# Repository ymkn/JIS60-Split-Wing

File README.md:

# JIS60-Split Wing

60% sized JIS layout split keyboard.

## Default Layout

Powered by RP2040 with [KMK Firmware](http://kmkfw.io/). Fully customizable.

## Build Guide

See [doc/build-guide.md](doc/build-guide.md)

## License

This project is licensed under the MIT License, see the [LICENSE file](LICENSE) for details.

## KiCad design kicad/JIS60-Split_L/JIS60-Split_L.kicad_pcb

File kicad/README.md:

# KiCAD source files

## KiCAD version

7.x or higher is required.

## dependencies

- https://github.com/crides/kleeb
  - rp2040-zero
- https://github.com/yskoht/kicad-MJ-4PP-9
  - TRRS Connector
- https://github.com/kiswitch/kiswitch
  - Keyswitch and Stab
- https://github.com/Salicylic-acid3/KiCAD_FootPrint
  - Mounting Hole

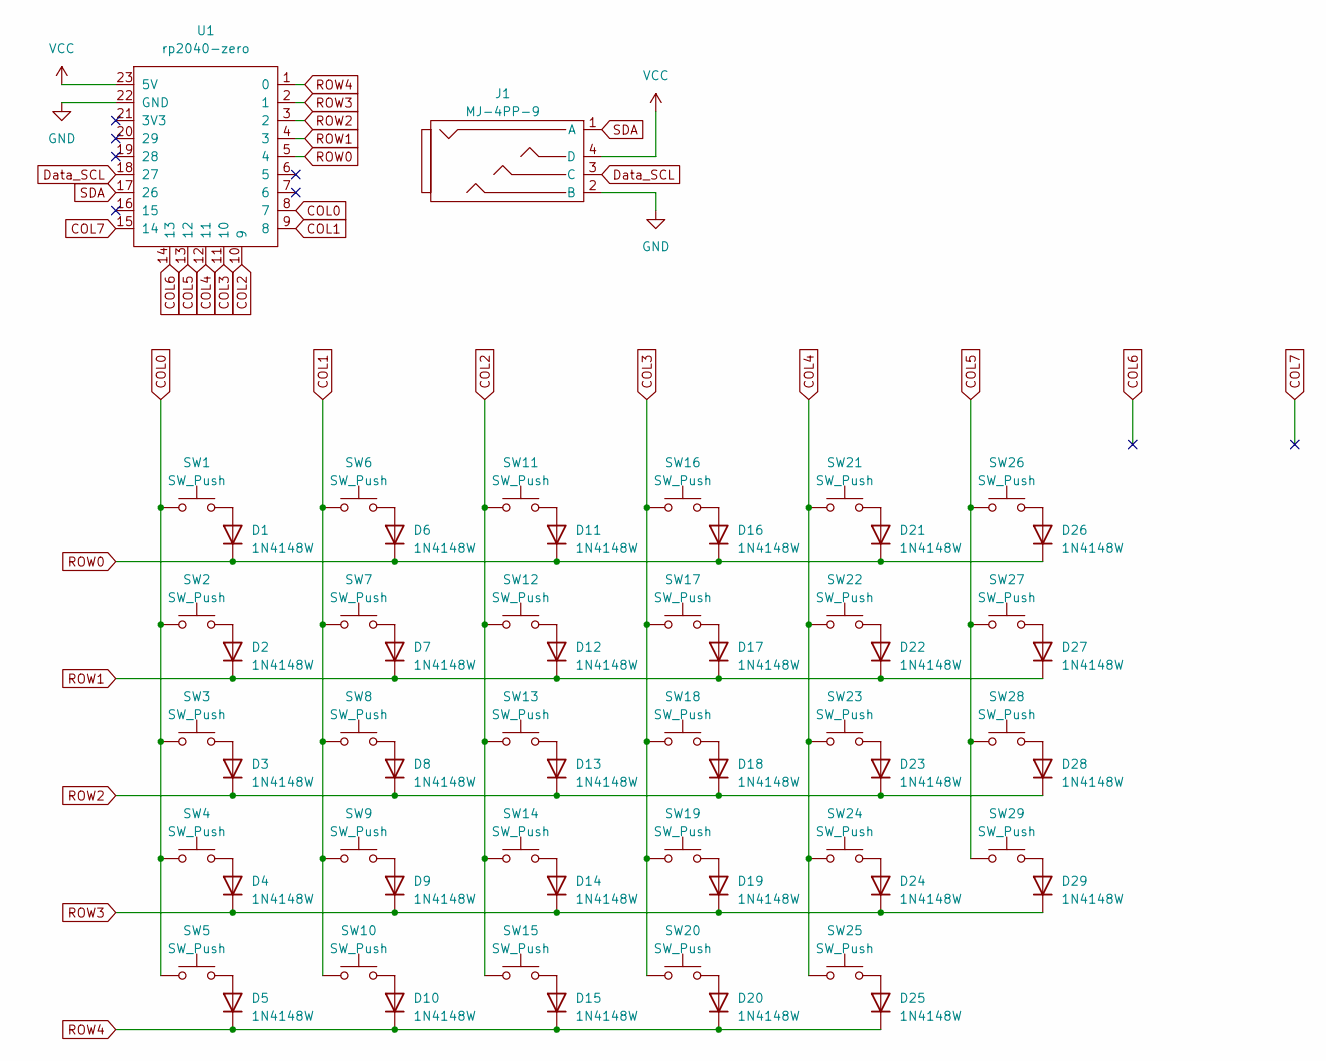
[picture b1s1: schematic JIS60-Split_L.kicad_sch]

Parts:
D1, D2, D3, D4, D5, D6, D7, D8, D9, D10, D11, D12, D13, D14, D15, D16, D17, D18, D19, D20, D21, D22, D23, D24, D25, D26, D27, D28, D29: 1N4148W; D_SOD-123
J1: MJ-4PP-9
SW1, SW6, SW7, SW8, SW9, SW11, SW12, SW13, SW14, SW16, SW17, SW18, SW19, SW21, SW22, SW23, SW24, SW26, SW27, SW28, SW29: SW_Push; SW_Hotswap_Kailh_MX_1.00u
SW2: SW_Push; SW_Hotswap_Kailh_MX_1.50u
SW3: SW_Push; SW_Hotswap_Kailh_MX_1.75u
SW4: SW_Push; SW_Hotswap_Kailh_MX_2.00u
SW5, SW10, SW15, SW20: SW_Push; SW_Hotswap_Kailh_MX_1.25u
SW25: SW_Push; SW_Hotswap_Kailh_MX_2.25u
U1: rp2040-zero; rp2040-zero-tht

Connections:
COL0: SW1.1, SW2.1, SW3.1, SW4.1, SW5.1, U1.8 (7)
COL1: SW6.1, SW7.1, SW8.1, SW9.1, SW10.1, U1.9 (8)
COL2: SW11.1, SW12.1, SW13.1, SW14.1, SW15.1, U1.10 (9)
COL3: SW16.1, SW17.1, SW18.1, SW19.1, SW20.1, U1.11 (10)
COL4: SW21.1, SW22.1, SW23.1, SW24.1, SW25.1, U1.12 (11)
COL5: SW26.1, SW27.1, SW28.1, SW29.1, U1.13 (12)
COL6: U1.14 (13)
COL7: U1.15 (14)
Data_SCL: J1.3 (C), U1.18 (27)
GND: J1.2 (B), U1.22 (GND)
unnamed: D1.2 (A), SW1.2
unnamed: D2.2 (A), SW2.2
unnamed: D3.2 (A), SW3.2
unnamed: D4.2 (A), SW4.2
unnamed: D5.2 (A), SW5.2
unnamed: D6.2 (A), SW6.2
unnamed: D7.2 (A), SW7.2
unnamed: D8.2 (A), SW8.2
unnamed: D9.2 (A), SW9.2
unnamed: D10.2 (A), SW10.2
unnamed: D11.2 (A), SW11.2
unnamed: D12.2 (A), SW12.2
unnamed: D13.2 (A), SW13.2
unnamed: D14.2 (A), SW14.2
unnamed: D15.2 (A), SW15.2
unnamed: D16.2 (A), SW16.2
unnamed: D17.2 (A), SW17.2
unnamed: D18.2 (A), SW18.2
unnamed: D19.2 (A), SW19.2
unnamed: D20.2 (A), SW20.2
unnamed: D21.2 (A), SW21.2
unnamed: D22.2 (A), SW22.2
unnamed: D23.2 (A), SW23.2
unnamed: D24.2 (A), SW24.2
unnamed: D25.2 (A), SW25.2
unnamed: D26.2 (A), SW26.2
unnamed: D27.2 (A), SW27.2
unnamed: D28.2 (A), SW28.2
unnamed: D29.2 (A), SW29.2
ROW0: D1.1 (K), D6.1 (K), D11.1 (K), D16.1 (K), D21.1 (K), D26.1 (K), U1.5 (4)
ROW1: D2.1 (K), D7.1 (K), D12.1 (K), D17.1 (K), D22.1 (K), D27.1 (K), U1.4 (3)
ROW2: D3.1 (K), D8.1 (K), D13.1 (K), D18.1 (K), D23.1 (K), D28.1 (K), U1.3 (2)
ROW3: D4.1 (K), D9.1 (K), D14.1 (K), D19.1 (K), D24.1 (K), D29.1 (K), U1.2 (1)
ROW4: D5.1 (K), D10.1 (K), D15.1 (K), D20.1 (K), D25.1 (K), U1.1 (0)
SDA: J1.1 (A), U1.17 (26)
VCC: J1.4 (D), U1.23 (5V)

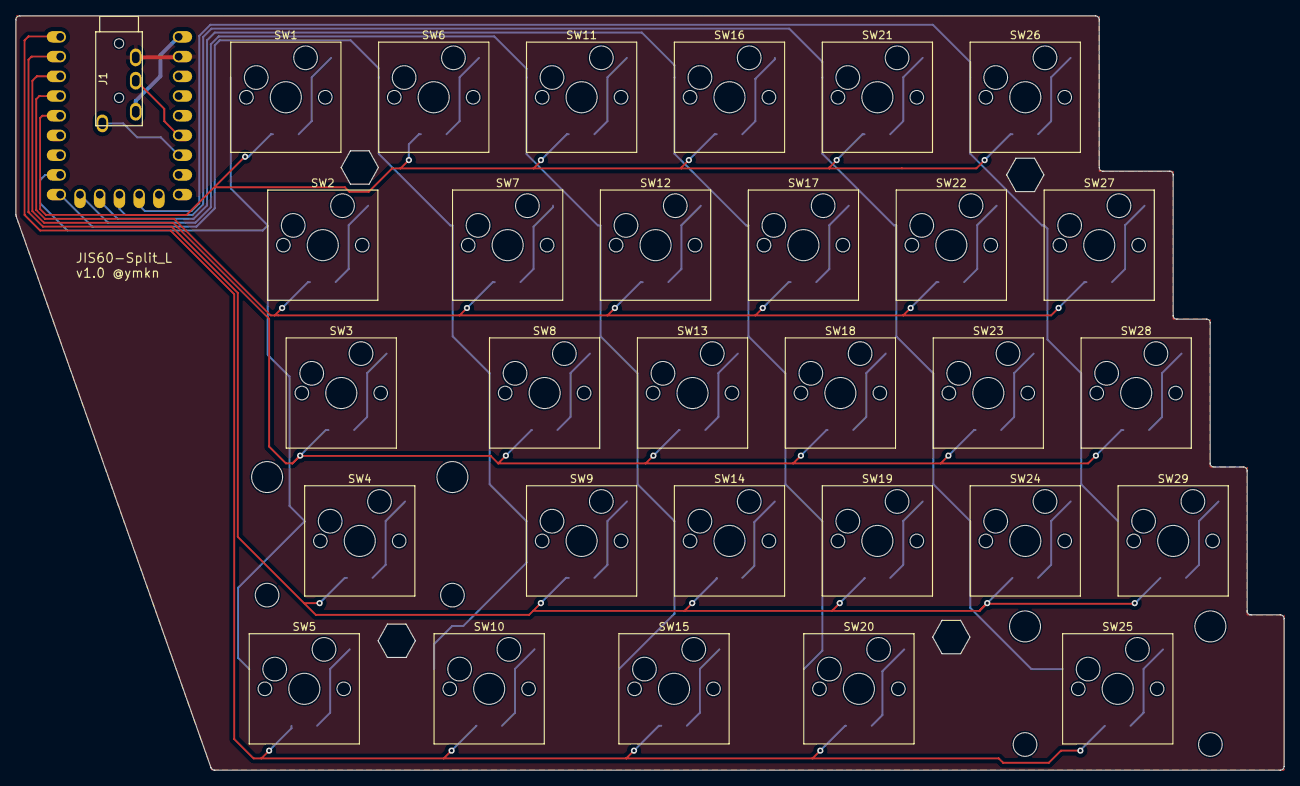
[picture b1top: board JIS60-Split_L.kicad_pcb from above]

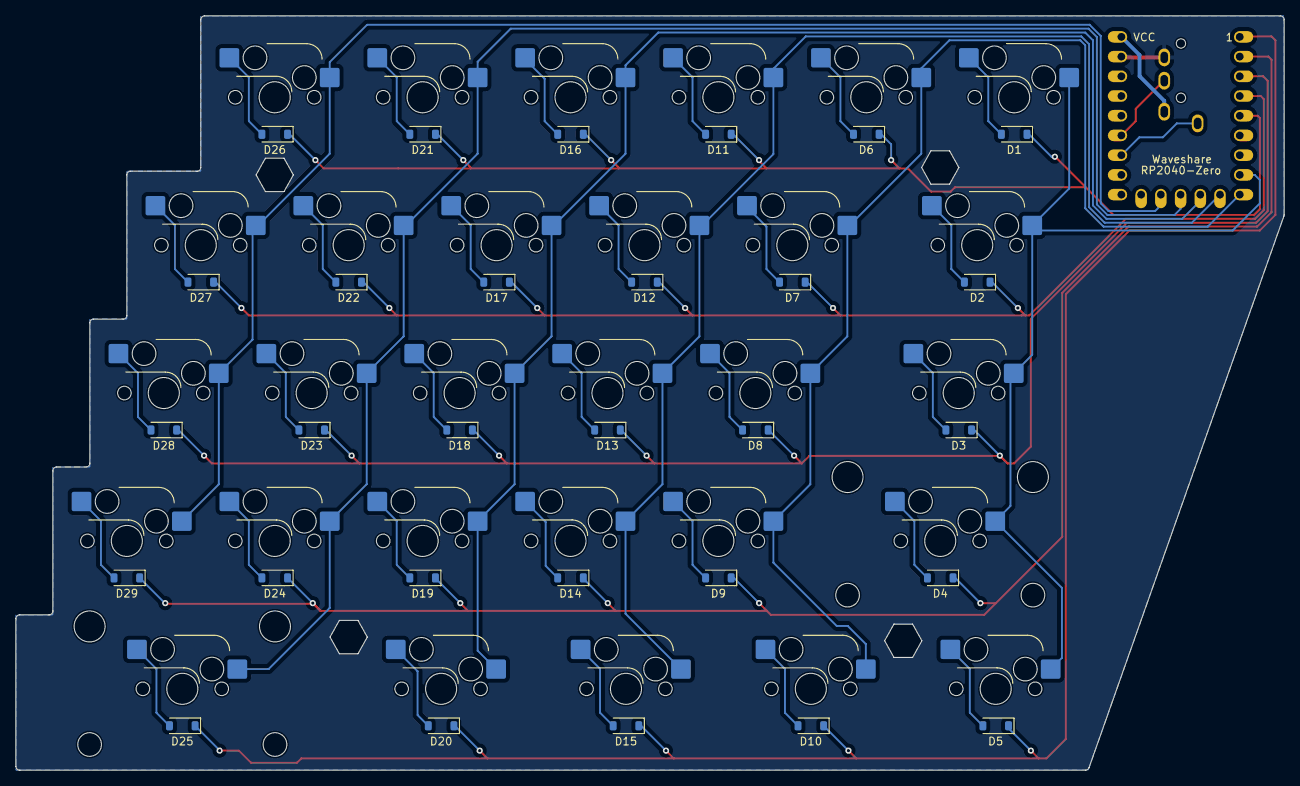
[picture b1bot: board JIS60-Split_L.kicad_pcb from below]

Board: 2 copper layers, 163.4 x 97.2 mm, 64 parts (30 on the bottom side), 44 nets.

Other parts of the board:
Ref**: Val**; m2_Spacer_Hole_hex
Ref**#2, Ref**#3, Ref**#4: Val**; m2_Spacer_Hole_hex

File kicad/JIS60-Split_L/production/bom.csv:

Designator,Footprint,Quantity,Value,LCSC Part #
"D1, D10, D11, D12, D13, D14, D15, D16, D17, D18, D19, D2, D20, D21, D22, D23, D24, D25, D26, D27, D28, D29, D3, D4, D5, D6, D7, D8, D9",D_SOD-123,29,1N4148W,
J1,MJ-4PP-9,1,MJ-4PP-9,
"SW1, SW11, SW12, SW13, SW14, SW16, SW17, SW18, SW19, SW21, SW22, SW23, SW24, SW26, SW27, SW28, SW29, SW6, SW7, SW8, SW9",SW_Hotswap_Kailh_MX_1.00u,21,SW_Push,
"SW10, SW15, SW20, SW5",SW_Hotswap_Kailh_MX_1.25u,4,SW_Push,
SW2,SW_Hotswap_Kailh_MX_1.50u,1,SW_Push,
SW25,SW_Hotswap_Kailh_MX_2.25u,1,SW_Push,
SW3,SW_Hotswap_Kailh_MX_1.75u,1,SW_Push,
SW4,SW_Hotswap_Kailh_MX_2.00u,1,SW_Push,
U1,rp2040-zero-tht,1,rp2040-zero,

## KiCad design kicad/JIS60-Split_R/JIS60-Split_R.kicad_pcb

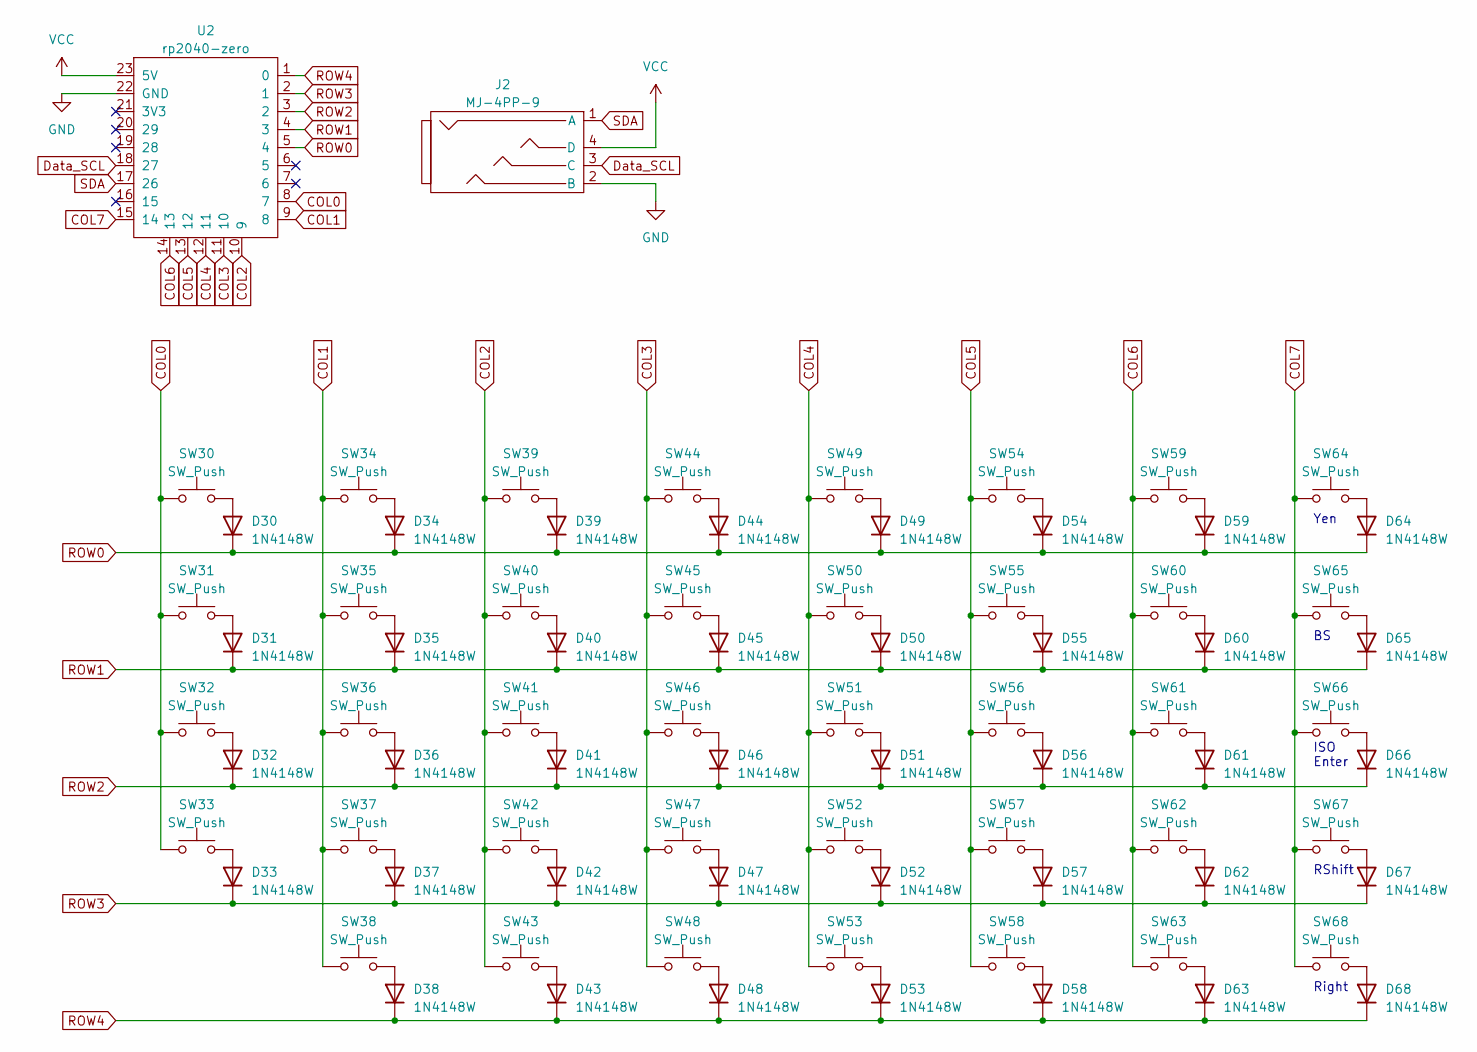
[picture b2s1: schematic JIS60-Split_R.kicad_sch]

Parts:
D30, D31, D32, D33, D34, D35, D36, D37, D38, D39, D40, D41, D42, D43, D44, D45, D46, D47, D48, D49, D50, D51, D52, D53, D54, D55, D56, D57, D58, D59, D60, D61, D62, D63, D64, D65, D66, D67, D68: 1N4148W; D_SOD-123
J2: MJ-4PP-9
SW30, SW31, SW32, SW33, SW34, SW35, SW36, SW37, SW38, SW39, SW40, SW41, SW42, SW44, SW45, SW46, SW47, SW49, SW50, SW51, SW52, SW54, SW55, SW56, SW57, SW58, SW59, SW60, SW61, SW62, SW63, SW64, SW65, SW67, SW68: SW_Push; SW_Hotswap_Kailh_MX_1.00u
SW43, SW48, SW53: SW_Push; SW_Hotswap_Kailh_MX_1.25u
SW66: SW_Push; SW_Hotswap_Kailh_MX_ISOEnter
U2: rp2040-zero; rp2040-zero-tht

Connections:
COL0: SW30.1, SW31.1, SW32.1, SW33.1, U2.8 (7)
COL1: SW34.1, SW35.1, SW36.1, SW37.1, SW38.1, U2.9 (8)
COL2: SW39.1, SW40.1, SW41.1, SW42.1, SW43.1, U2.10 (9)
COL3: SW44.1, SW45.1, SW46.1, SW47.1, SW48.1, U2.11 (10)
COL4: SW49.1, SW50.1, SW51.1, SW52.1, SW53.1, U2.12 (11)
COL5: SW54.1, SW55.1, SW56.1, SW57.1, SW58.1, U2.13 (12)
COL6: SW59.1, SW60.1, SW61.1, SW62.1, SW63.1, U2.14 (13)
COL7: SW64.1, SW65.1, SW66.1, SW67.1, SW68.1, U2.15 (14)
Data_SCL: J2.3 (C), U2.18 (27)
GND: J2.2 (B), U2.22 (GND)
unnamed: D30.2 (A), SW30.2
unnamed: D31.2 (A), SW31.2
unnamed: D32.2 (A), SW32.2
unnamed: D33.2 (A), SW33.2
unnamed: D34.2 (A), SW34.2
unnamed: D35.2 (A), SW35.2
unnamed: D36.2 (A), SW36.2
unnamed: D37.2 (A), SW37.2
unnamed: D38.2 (A), SW38.2
unnamed: D39.2 (A), SW39.2
unnamed: D40.2 (A), SW40.2
unnamed: D41.2 (A), SW41.2
unnamed: D42.2 (A), SW42.2
unnamed: D43.2 (A), SW43.2
unnamed: D44.2 (A), SW44.2
unnamed: D45.2 (A), SW45.2
unnamed: D46.2 (A), SW46.2
unnamed: D47.2 (A), SW47.2
unnamed: D48.2 (A), SW48.2
unnamed: D49.2 (A), SW49.2
unnamed: D50.2 (A), SW50.2
unnamed: D51.2 (A), SW51.2
unnamed: D52.2 (A), SW52.2
unnamed: D53.2 (A), SW53.2
unnamed: D54.2 (A), SW54.2
unnamed: D55.2 (A), SW55.2
unnamed: D56.2 (A), SW56.2
unnamed: D57.2 (A), SW57.2
unnamed: D58.2 (A), SW58.2
unnamed: D59.2 (A), SW59.2
unnamed: D60.2 (A), SW60.2
unnamed: D61.2 (A), SW61.2
unnamed: D62.2 (A), SW62.2
unnamed: D63.2 (A), SW63.2
unnamed: D64.2 (A), SW64.2
unnamed: D65.2 (A), SW65.2
unnamed: D66.2 (A), SW66.2
unnamed: D67.2 (A), SW67.2
unnamed: D68.2 (A), SW68.2
ROW0: D30.1 (K), D34.1 (K), D39.1 (K), D44.1 (K), D49.1 (K), D54.1 (K), D59.1 (K), D64.1 (K), U2.5 (4)
ROW1: D31.1 (K), D35.1 (K), D40.1 (K), D45.1 (K), D50.1 (K), D55.1 (K), D60.1 (K), D65.1 (K), U2.4 (3)
ROW2: D32.1 (K), D36.1 (K), D41.1 (K), D46.1 (K), D51.1 (K), D56.1 (K), D61.1 (K), D66.1 (K), U2.3 (2)
ROW3: D33.1 (K), D37.1 (K), D42.1 (K), D47.1 (K), D52.1 (K), D57.1 (K), D62.1 (K), D67.1 (K), U2.2 (1)
ROW4: D38.1 (K), D43.1 (K), D48.1 (K), D53.1 (K), D58.1 (K), D63.1 (K), D68.1 (K), U2.1 (0)
SDA: J2.1 (A), U2.17 (26)
VCC: J2.4 (D), U2.23 (5V)

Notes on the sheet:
ISO Enter
RShift
Yen
Right

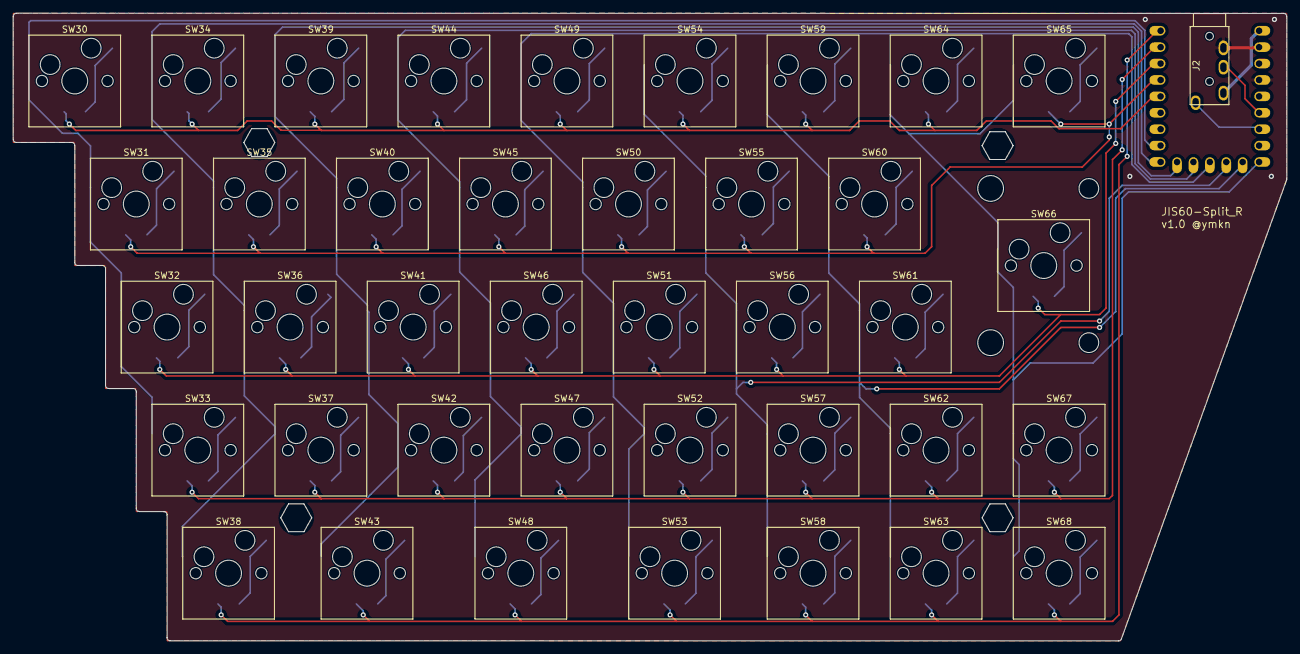
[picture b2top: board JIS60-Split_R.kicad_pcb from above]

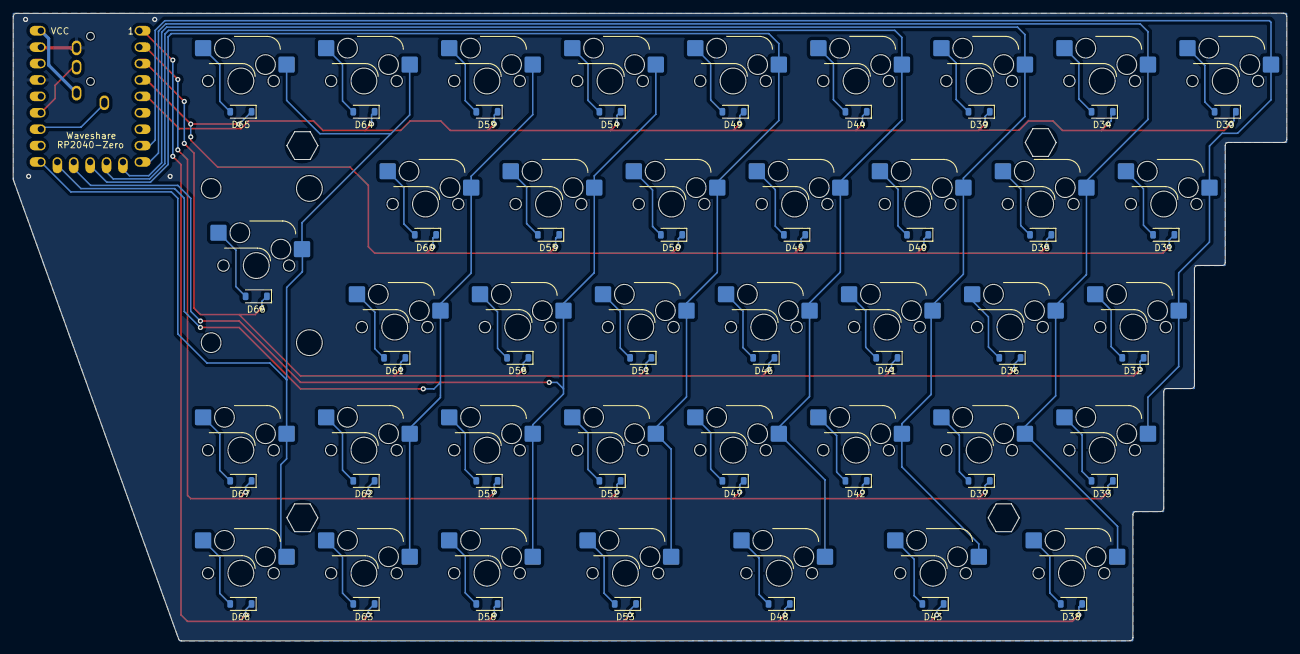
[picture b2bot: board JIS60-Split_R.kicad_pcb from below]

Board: 2 copper layers, 197.2 x 97.2 mm, 84 parts (40 on the bottom side), 56 nets.

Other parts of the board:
Ref**: Val**; m2_Spacer_Hole_hex
Ref**#2, Ref**#3, Ref**#4: Val**; m2_Spacer_Hole_hex

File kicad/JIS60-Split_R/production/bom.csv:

Designator,Footprint,Quantity,Value,LCSC Part #
"D30, D31, D32, D33, D34, D35, D36, D37, D38, D39, D40, D41, D42, D43, D44, D45, D46, D47, D48, D49, D50, D51, D52, D53, D54, D55, D56, D57, D58, D59, D60, D61, D62, D63, D64, D65, D66, D67, D68",D_SOD-123,39,1N4148W,
J2,MJ-4PP-9,1,MJ-4PP-9,
"SW30, SW31, SW32, SW33, SW34, SW35, SW36, SW37, SW38, SW39, SW40, SW41, SW42, SW44, SW45, SW46, SW47, SW49, SW50, SW51, SW52, SW54, SW55, SW56, SW57, SW58, SW59, SW60, SW61, SW62, SW63, SW64, SW65, SW67, SW68",SW_Hotswap_Kailh_MX_1.00u,35,SW_Push,
"SW43, SW48, SW53",SW_Hotswap_Kailh_MX_1.25u,3,SW_Push,
SW66,SW_Hotswap_Kailh_MX_ISOEnter,1,SW_Push,
U2,rp2040-zero-tht,1,rp2040-zero,
